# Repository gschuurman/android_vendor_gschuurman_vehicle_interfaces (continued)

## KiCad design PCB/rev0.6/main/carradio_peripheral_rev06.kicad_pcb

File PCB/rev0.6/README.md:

# PCB rev 0.6: main board with a K-line module socket

Rev 0.6 is rev 0.5 (`../rev0.5/`, kept as the reference) plus a socket for a stackable K-line module. The GNSS and
audio modules are the rev 0.4 boards (`../rev0.4/gnss|audio`); the USB module is `usb/` (rev 0.4 with the fix below). Everything in
`../rev0.5/README.md` (USB_UP pair, TPS560430 layout, expansion pins) and `../rev0.4/README.md` still applies except
J10 and the VIM3 power key, described here.

Everything to order and hand-assemble the four boards is in `order/` (see `order/ORDER_INSTRUCTIONS.md`); `fab/` holds
the same Gerbers plus JLC assembly BOM/CPL files in case of a PCBA order.

## USB module rev 0.6

`usb/carradio_usb_rev06.*` is the rev 0.4 USB module with solid zone connections on the GND pads of the 5 V / 3 A buck
U15 (LMR33630, pin 1 and the PowerPAD), the port switch U16 (TPS2561, pin 1 and the exposed pad) and C69. KiCad 10 had
flagged them as starved thermals. DRC: 0 unconnected, no errors.

## Impedance-controlled pairs (JLCPCB calculator)

JLCPCB's impedance calculator for JLC04161H-7628 (L1 over L2) gives 0.334 / 0.300 mm for 90 Ω and 0.2187 / 0.20 mm
for 100 Ω edge-coupled pairs. Rev 0.6 uses them:

- **USB_UP** (VIM3 to hub 1): re-routed at **0.32 mm / 0.30 mm gap** (rev 0.5: 0.30 / 0.15; the tight gap put it
  below 90 Ω). 0.32 instead of 0.334 so the pair fits the gap between U13's pins and the J23 socket; that is about 1 Ω
  higher. DP 51.3 mm, DM 53.2 mm. The In1 keep-out under it is 0.5 mm each side, opened at U13's pin escapes and for
  two vias beside the pair (`pairkeep.py` BUF / EXCLUDE_FP / EXCLUDE_XY).
- **HDMI** D0, D1, D2, CLK (J13 to J14): rebuilt by `hdmipairs.py` as coupled **0.2187 mm / 0.20 mm** pairs. Before
  they were 0.20 mm traces 0.80 mm apart (about 140 Ω, each trace closer to the neighbouring pair than to its partner).
  Each pair now runs centred over its GND pin with a short 45° jog at both connectors; P/N lengths match within 0.69 mm
  (about 5 ps).
- Net classes in the project: USB 0.32 / 0.30, HDMI 0.2187 / 0.20.

## J10: K-line module socket

In rev 0.5, J10 was a 1x8 male header under the USB module with no battery voltage. Now it is a **2x4 female socket,
8.5 mm tall** (same family as J23/J25/J27) at (82, 29) mm, in the free strip between the HDMI pairs and the USB module.
A K-line module stacks on it like the other modules: male header on its underside, about 11 mm above the main board,
held by one **M2 standoff at H8 (69.6, 18.5)**.

| Pin | Net | Pin | Net |
|---|---|---|---|
| 1 | +3V3_MCU | 2 | GND |
| 3 | EXP_GP32: RP2350B UART TX (to the transceiver TXD) | 4 | EXP_GP33: UART RX (from RXD) |
| 5 | EXP_GP28: enable / sleep, or an L-line driver | 6 | GND |
| 7 | VBAT_KLINE: protected battery voltage through F6 | 8 | +5V_AON (if the transceiver wants 5 V) |

- **F6** (BHFUSE BSMD1206-020-30V, LCSC C883118, 200 mA hold / 460 mA trip) feeds pin 7 from VBAT_P (after the
  reverse-polarity diode and load-dump TVS). A fault on the module trips F6, not F1, so the always-on 5 V supply and
  the MCU keep running.
- **Module outline:** up to about 25 x 17 mm, over x 67-91, y 15-32 mm on the main board. That clears the HDMI
  connector J13 (top), the screen FPC J14 and its latch (right edge) and the USB module (below y 32.5). The parts under
  it are low SMD parts and the HDMI pairs, which the module only flies over. Socket pin 1 is at (78.19, 27.63).
- **Car side:** the module brings the K-line in through its own connector, e.g. a JST to the OBD-II socket
  (pin 7 K-line, pins 4/5 GND). Pin 16 is not needed because VBAT comes from J10 pin 7.
- **Transceiver:** a K-line part such as ST L9637D or a LIN transceiver such as TJA1021 (LIN is electrically close and
  often used for K-line at 10.4 kbaud). Check that TXD accepts 3.3 V logic and RXD is open-drain or 3.3 V compatible;
  pull RXD up to J10 pin 1.
- **Firmware:** UART on GPIO32/33 at 10.4 kbaud; for the ISO 9141 / KWP2000 slow init, switch GPIO32 to SIO and
  bit-bang the 5-baud address byte. GPIO28 drives enable/sleep.

The socket and standoff stay outside the HDMI corridor (In1 "HDMI reference" keep-out), so the HDMI ground reference
is untouched. J21 (SPI1 + I2C under the USB module) is unchanged from rev 0.5.

## VIM3 power key: PhotoMOS U22

The VIM3 POWER key is pressed by a PhotoMOS that shorts the key's own two pins, isolated, as in the earlier hand-wired
setup. Up to rev 0.5, Q1 (AO3400A) pulled J5 pin 1 to the board's GND.

- **U22**: Panasonic **AQY210S** (SOP-4, 350 V / 120 mA, 25 Ω max on), on the **bottom side** right next to J5 at
  (19.2, 15.0). Pins 3/4 (the switch) go to J5 pins 1/2 over a few mm of bottom copper; pin 2 (LED cathode) to GND.
- **R12**: 390 Ω from GPIO15 (`MCU_PWR_KEY`) to the LED anode, about 5 mA from 3.3 V. The AQY210S needs 3 mA at most
  to switch on. The GPIO's default 4 mA drive is fine; the 8 mA setting gives more margin. Firmware is unchanged:
  GPIO15 high = key pressed.
- **R19** (the MOSFET's gate pull-down) is gone: an undriven LED is off.
- **J5** (JST-PH 2P): pins 1 and 2 go to the two pads of the VIM3 POWER key. Either way round works, J5 no longer
  carries GND.
- Scripts: `layout/schematic/pwrkey_sch.py` (schematic) and `layout/main/pwrkeypcb.py` (place U22, rip the old
  copper), then `bridge.py` routed `/VIM3_PWR_KEY_A`, `/VIM3_PWR_KEY_B` and `/PWR_KEY_LED`. DRC: 0 unconnected, no
  errors; schematic parity unchanged (field mismatches only).

## Status

- Main board: DRC 0 unconnected, no errors (warnings: silkscreen, unused fan-out stubs); schematic parity same as rev 0.5.
- USB module rev 0.6: DRC 0 unconnected, no errors. GNSS module: clean. Audio module: one starved-thermal warning on
  the through-hole header J24 pin 3 (fine for hand soldering).

## Bring-up wizards

Step-by-step bench wizards (multimeter first, then first power): `main/WIZARD.html`, `usb/WIZARD.html`,
`../rev0.4/gnss/WIZARD.html` and `../rev0.4/audio/WIZARD.html`. See `../wizard/README.md`.

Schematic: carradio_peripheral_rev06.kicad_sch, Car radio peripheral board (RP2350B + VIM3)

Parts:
C1, C49, C50: 10uF 50V; C_1206_3216Metric; MPN 1206 10uF 50V X5R (Murata GRM31CR61H106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; LCSC C77092
C2, C3, C5, C6, C7, C8, C9, C10, C11, C42, C43, C44, C45, C47, C51, C52, C63, C85, C86, C87, C88, C89, C90, C91, C92, C93, C94, C95, C96, C97, C98, C101, C102, C103: 100nF; C_0603_1608Metric; MPN 0603 100nF 50V X7R; LCSC C14663
C4, C56, C57, C58, C59: 22uF; C_0805_2012Metric; MPN 0805 22uF 25V X5R; LCSC C45783
C12, C13, C61, C80: 1uF; C_0603_1608Metric; MPN 0603 1uF 50V X5R (Murata GRM188R61H105K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; LCSC C77386
C46, C62, C81: 10uF; C_0805_2012Metric; MPN 0805 10uF 25V X5R; LCSC C15850
C48: 100uF 50V; CP_Elec_8x10; MPN Panasonic EEEFK1H101P 100uF 50V 8x10.2; LCSC C178548
C53, C82, C83, C84: 4.7uF; C_0603_1608Metric; MPN 0603 4.7uF 16V X5R; LCSC C19666
C54: 4.7nF; C_0603_1608Metric; MPN 0603 4.7nF 50V X7R; LCSC C53987
C55: 22pF; C_0603_1608Metric; MPN 0603 22pF 50V C0G; LCSC C1653
C60: 220uF 10V polymer; CP_Elec_6.3x7.7; MPN Lelon OVZ221M1CTR-0608 polymer 220uF 16V; LCSC C881921
C99, C100: 15pF; C_0603_1608Metric; MPN Samsung CL10C150JB8NNNC 15pF C0G; LCSC C1644
C104: 1nF; C_0603_1608Metric; MPN Samsung CL10B102KB8NNNC 0603 1nF 50V X7R; LCSC C1588
D1, D4, D9: SS34; D_SMA; MPN SS34 40V 3A Schottky; LCSC C8678
D2, D5, D13: SMBJ22A; D_SMB; MPN SMBJ22A (BORN); alt DOWO C284010; LCSC C151920
D6, D7, D11, D12: 1N4148W; D_SOD-123; MPN 1N4148W; LCSC C81598
D8, D15: BZT52C12; D_SOD-123; MPN BZT52C12-7-F 12V zener; LCSC C124196
D10, D16: LED green; LED_0805_2012Metric; MPN KT-0805G green LED; LCSC C2297
D14: Load-dump TVS; D_SMC; MPN Liown 5.0SMDJ22A, 5 kW SMC; LCSC C2990362
F1, F3: PTC 0.5A hold 30V; Fuse_1206_3216Metric; MPN BHFUSE BSMD1206-050-30V; LCSC C883126
F2: PTC 0.75A hold 30V; Fuse_1812_4532Metric; MPN Littelfuse 1812L075/33DR; LCSC C151170
F4: 7.5A fuse; Littelfuse_01530008Z; MPN Littelfuse 01530008Z mini blade holder 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; LCSC C206907
F6: PTC 0.2A hold 30V; Fuse_1206_3216Metric; MPN BHFUSE BSMD1206-020-30V; LCSC C883118
J1: ISO 10487 A (via pigtail); Molex_Micro-Fit_3.0_43045-0812_2x04_P3.00mm_Vertical; MPN Molex 43045-0812; LCSC C277661
J2: VIM3 40-pin via 2x20 IDC ribbon; IDC-Header_2x20_P2.54mm_Vertical; MPN BOOMELE 2.54-2*20P box header (check it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; LCSC C9138
J5: VIM3 POWER key lead; JST_PH_B2B-PH-K_1x02_P2.00mm_Vertical; MPN JST B2B-PH-K-S; LCSC C131337
J7: BH1750 light sensor; JST_PH_B4B-PH-K_1x04_P2.00mm_Vertical; MPN JST B4B-PH-K-S; LCSC C131334
J8: ISO 10487 C1 (via pigtail); Molex_Micro-Fit_3.0_43045-0612_2x03_P3.00mm_Vertical; MPN Molex 43045-0612; LCSC C234188
J10: K-line module socket; PinSocket_2x04_P2.54mm_Vertical; MPN 2x4 2.54mm female socket, 8.5mm body (s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
J12: Display buttons; JST_PH_B5B-PH-K_1x05_P2.00mm_Vertical; MPN JST B5B-PH-K-S; LCSC C157993
J13: HDMI in (from VIM3); HDMI_A_Amphenol_10029449-x01xLF_Horizontal; MPN Amphenol 10029449-111RLF (plating varia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; LCSC C427307
J14: Display FPC 40P 0.5mm; XUNPU_FPC-05FB-40PH20; MPN XUNPU FPC-05FB-40PH20, 40P 0.5mm dual-c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; LCSC C2856837
J18: VIM3 VIN (JST-XH 2P); JST_XH_B2B-XH-A_1x02_P2.50mm_Vertical; MPN JST B2B-XH-A; LCSC C158012
J21: Expansion 2; PinHeader_1x10_P2.54mm_Vertical; MPN BOOMELE 1x10 male header 2.54mm; LCSC C57369
J22: SWD; PinHeader_1x04_P2.54mm_Vertical; MPN 1x4 male header 2.54mm; LCSC C124378
J23: Audio module socket; PinSocket_2x10_P2.54mm_Vertical; MPN BOOMELE 2.54-2*10P female 8.5mm (LCSC o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; LCSC C30867
J25: USB module socket; PinSocket_2x10_P2.54mm_Vertical; MPN BOOMELE 2.54-2*10P female 8.5mm (LCSC o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; LCSC C30867
J27: GNSS module socket; PinSocket_2x08_P2.54mm_Vertical; MPN 2x8 2.54mm female socket, 8.5mm body (s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
JP1: SERVICE jumper; PinHeader_1x02_P2.54mm_Vertical; MPN 1x2 male header 2.54mm + jumper cap C53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; LCSC C124375
JP2: GNSS RX source; SolderJumper-3_P1.3mm_Bridged12_RoundedPad1.0x1.5mm; MPN 3-pad solder jumper (PCB copper, no par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
L1: 18uH; L_Sunlord_SWPA4030S; MPN SWPA4030S180MT 18uH; LCSC C96895
L3: 4.7uH 12A+; L_Bourns_SRP1245A; MPN Bourns SRP1265A-4R7M 4.7uH Isat 28A 8.4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; LCSC C780205
L5: 3.3uH; L_Murata_DFE201610P; MPN Abracon AOTA-B201610S3R3-101-T 3.3uH (R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; LCSC C42411119
NT1, NT2, NT3: NetTie; NetTie-2_SMD_Pad0.5mm; MPN net tie (copper only, not a part)
Q2: P-MOSFET -60V; SOT-23; MPN onsemi FDN5618P -60V P-MOSFET (check 1=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; LCSC C400792
Q3: 2N7002; SOT-23; MPN JSCJ 2N7002; LCSC C8545
Q10: P-MOSFET -40V; TO-252-2; MPN NCE40P70K -40V 10 mOhm P-MOSFET TO-252 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; LCSC C130101
Q11, Q12: CSD18543Q3A; VSON-8_3.3x3.3mm_P0.65mm_NexFET; MPN TI CSD18543Q3A 60V 8.5mOhm N-MOSFET; LCSC C840100
R1, R15, R35, R70, R72, R96: 100k; R_0603_1608Metric; MPN 0603 100k 1%; LCSC C25803
R2: 24k; R_0603_1608Metric; MPN 0603 24k 1%; LCSC C23352
R3, R5, R29, R31: 4.7kΩ 0805; R_0805_2012Metric; MPN 0805 4.7k 1%; LCSC C17673
R4, R6, R8, R9, R18, R30, R32, R33, R34, R94, R95: 4.7k; R_0603_1608Metric; MPN 0603 4.7k 1%; LCSC C23162
R7, R37, R38, R39, R40, R46, R59, R61, R63, R65, R73, R79, R81, R82, R86, R90, R100, R101: 1k; R_0603_1608Metric; MPN 0603 1k 1%; LCSC C21190
R10: 1M; R_0603_1608Metric; MPN 0603 1M 1%; LCSC C22935
R11: 220k; R_0603_1608Metric; MPN 0603 220k 1%; LCSC C22961
R12: 390Ω; R_0603_1608Metric; MPN UNI-ROYAL 0603WAF3900T5E 390 1%; LCSC C23151
R13, R14, R47, R58, R60, R62, R64, R66, R85, R87, R88, R89, R91, R92, R93, R104: 10k; R_0603_1608Metric; MPN 0603 10k 1%; LCSC C25804
R16, R23, R24: 100Ω; R_0603_1608Metric; MPN 0603 100 1%; LCSC C22775
R42, R43, R44, R45, R80: 33Ω; R_0603_1608Metric; MPN 0603 33 1%; LCSC C23140
R56, R67: 0Ω; R_0603_1608Metric; MPN 0603 0 1%; LCSC C21189
R57: 0Ω; R_0603_1608Metric; MPN 0603 0 1%; LCSC C21189; not fitted
R68: 47k; R_0603_1608Metric; MPN 0603 47k 1% (YAGEO RC0603FR-0747KL); LCSC C105579
R69: 30k; R_0603_1608Metric; MPN UNI-ROYAL 0603WAF3002T5E; LCSC C22984
R71: 8.2k; R_0603_1608Metric; MPN 0603 8.2k 1%; LCSC C25981
R74: 10mΩ 2512; R_2512_6332Metric; MPN Yageo PA2512FKE7T0R01E 10 mOhm 1% 3W; LCSC C375691
R83, R84: 27Ω; R_0603_1608Metric; MPN FOJAN FRC0603F27R0TS 27R 1%; LCSC C2907021
R97, R98: 0Ω; R_0402_1005Metric; MPN UNI-ROYAL 0402WGF0000TCE 0402 0R; LCSC C17168
R99: 2.2Ω 0805; R_0805_2012Metric; MPN UNI-ROYAL 0805W8F220KT5E 0805 2.2R 125mW; LCSC C17521
SW1: BOOTSEL; SW_SPST_TL3342; MPN E-Switch TL3342F160QG; LCSC C2886898
SW2: RESET; SW_SPST_TL3342; MPN E-Switch TL3342F160QG; LCSC C2886898
TH1: NTC 10k B3950; R_0603_1608Metric; MPN Murata NCP18XH103F03RB 10k B3380 0603; LCSC C13564
U1: TPS560430XDBVR; SOT-23-6; MPN TPS560430XDBVR 36V 600mA buck, 1.1MHz; LCSC C524782
U2, U3, U4, U5: EL817S1(C); SMDIP-4_W7.62mm; MPN EL817S1(C)(TU)-F (EL817S1(C)(TU)-FV); LCSC C470884
U6: LP5907MFX-3.3; SOT-23-5; MPN TI LP5907MFX-3.3/NOPB 250mA LDO (TECH P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; LCSC C5370990
U12: TPS55288RPMR; TPS55288RPMR_VQFN-HR-26; MPN TI TPS55288RPMR; LCSC C2864583
U13: CH334R; QSOP-16_3.9x4.9mm_P0.635mm; MPN WCH CH334R 4-port USB 2.0 hub, QSOP-16; LCSC C4154405
U19: AP2112K-3.3; SOT-23-5; MPN Diodes AP2112K-3.3TRG1; LCSC C51118
U20: RP2350B; QFN-80-1EP_10x10mm_P0.4mm_EP3.4x3.4mm; MPN Raspberry Pi RP2350B QFN-80 (LCSC stock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; LCSC C42415655
U21: W25Q128JVS; SOIC-8_5.3x5.3mm_P1.27mm; MPN Winbond W25Q128JVSIQ; LCSC C97521
U22: AQY210S; SO-4_4.4x4.3mm_P2.54mm; MPN Panasonic AQY210S PhotoMOS 350V 120mA 1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
Y1: 12MHz; Crystal_SMD_3225-4Pin_3.2x2.5mm; MPN YXC X322512MSB4SI 12MHz; LCSC C9002
Y3: 12MHz; Crystal_SMD_3225-4Pin_3.2x2.5mm; MPN Abracon ABM8-272-T3 12MHz (Raspberry Pi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; LCSC C20625731

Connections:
/+1V1_MCU: C83.1, C93.1, C94.1, C95.1, L5.2, U20.10 (DVDD), U20.32 (DVDD), U20.51 (DVDD), U20.65 (VREG_FB)
/+3V3_GNSS: C13.1, J27.1, J27.2, U6.5 (OUT)
/+3V3_MCU: C8.1, C81.1, C82.1, C85.1, C86.1, C87.1, C88.1, C89.1, C90.1, C91.1, C92.1, C96.1, C97.1, C98.1, J7.1, J10.1, J21.1, J27.4, JP1.1, R33.1, R34.1, R58.1, R60.1, R62.1, R64.1, R80.1, R85.1, R87.1, R88.1, R89.1, R93.1, U2.4, U3.4, U4.4, U5.4, U19.5 (VOUT), U20.5 (IOVDD), U20.15 (IOVDD), U20.24 (IOVDD), U20.29 (IOVDD), U20.41 (IOVDD), U20.50 (IOVDD), U20.59 (ADC_AVDD), U20.60 (IOVDD), U20.64 (VREG_VIN), U20.68 (USB_OTP_VDD), U20.69 (QSPI_IOVDD), U20.76 (IOVDD), U21.8 (VCC)
/+5V_AON: C4.1, C12.1, C61.1, C80.1, J10.8, L1.2, R1.1, U6.1 (IN), U13.12 (V5), U19.1 (VIN), U19.3 (EN)
/+5V_SYS: C46.1, C47.1, J14.4, J14.5, J14.6, J18.1, J25.5, J25.6, NT2.2, R74.2, R91.1
/ACC_F: D4.2 (A), F2.2
/ACC_LED: D6.1 (K), R3.2, U2.1
/ACC_P: C5.1, D4.1 (K), D5.1 (K), D8.1 (K), Q2.2 (S), R3.1, R13.1, R31.1
/ACC_RAW: F2.1, J1.7
/AMP_CTRL: Q3.1 (G), R15.1, R16.2
/AMP_G: D8.2 (A), Q2.1 (G), R13.2, R14.1
/AMP_LED: D10.2 (A), R18.2
/AMP_PULL: Q3.3 (D), R14.2
/AMP_REM: D9.1 (K), D13.1 (K), F3.2, J1.3, J8.6, R18.1, R57.1
/AMP_SW: F3.1, Q2.3 (D)
/BATT_F: D1.2 (A), F1.2
/BATT_F2: F4.2, Q10.2 (D)
/BATT_RAW: F1.1, F4.1, J1.4
/BB_AGND: C54.2, C55.2, NT3.1, R67.2, R68.2, R69.2, R70.2, U12.7 (DITH/SYNC), U12.10 (AGND)
/BB_BOOT1: C51.1, U12.22 (BOOT1)
/BB_BOOT2: C52.1, U12.20 (BOOT2)
/BB_CDC: R70.1, U12.16 (CDC)
/BB_COMP: C55.1, R71.1, U12.18 (COMP)
/BB_COMP_RC: C54.1, R71.2
/BB_DR1H: R97.1, U12.2 (DR1H)
/BB_DR1H_G: Q11.4 (G), R97.2
/BB_DR1L: R98.1, U12.1 (DR1L)
/BB_DR1L_G: Q12.4 (G), R98.2
/BB_FSW: R68.1, U12.8 (FSW)
/BB_ILIM: R69.1, U12.17 (ILIM)
/BB_ISN: NT2.1, U12.13 (ISN)
/BB_ISP: NT1.1, U12.12 (ISP)
/BB_MODE: R67.1, U12.15 (MODE)
/BB_SNUB: C104.2, R99.1
/BB_SW1: C51.2, C104.1, L3.1, Q11.1 (S), Q11.2 (S), Q11.3 (S), Q12.5 (D), U12.23 (SW1)
/BB_SW2: C52.2, L3.2, U12.21 (SW2), U12.25 (SW2)
/BB_VCC: C53.1, U12.19 (VCC)
/BB_VOUT: C56.1, C57.1, C58.1, C59.1, C60.1, NT1.2, R74.1, U12.11 (VOUT), U12.26 (VOUT)
/BL_EN: J14.37, R23.2
/BL_PWM: J14.36, R24.2
/BOOTSEL_SW: R81.2, SW1.1
/BTN_MUTE: J12.4, R65.1
/BTN_SCREEN: J12.1, R59.1
/BTN_VOLDN: J12.3, R63.1
/BTN_VOLUP: J12.2, R61.1
/BUCK_CB: C3.1, U1.1 (CB)
/BUCK_FB: R1.2, R2.1, U1.3 (FB)
/BUCK_SW: C3.2, L1.1, U1.6 (SW)
/DAC_XSMT: J23.12, R46.2, R47.1
/EXP_GP24: J21.9, U20.25 (GPIO24)
/EXP_GP25: J21.8, U20.26 (GPIO25)
/EXP_GP26: J21.7, U20.27 (GPIO26)
/EXP_GP27: J21.6, U20.28 (GPIO27)
/EXP_GP28: J10.5, U20.36 (GPIO28)
/EXP_GP32: J10.3, U20.40 (GPIO32)
/EXP_GP33: J10.4, U20.42 (GPIO33)
/GNSS_PPS: J27.14, R40.1
/GNSS_RST: J27.13, R39.2
/GNSS_RXD: J27.10, JP2.2 (C)
/GNSS_RXD_MCU: JP2.3 (B), R37.2
/GNSS_RXD_VIM: JP2.1 (A), R101.2
/GNSS_SAFEBOOT: J27.15, R79.2
/GNSS_TXD: J27.8, R38.1, R100.1
/GNSS_USB_DM: J27.9, U13.3 (DM3-)
/GNSS_USB_DP: J27.7, U13.4 (DP3+)
/HDMI_5V: J13.18 (+5V), J14.27
/HDMI_CEC: J13.13 (CEC), J14.23
/HDMI_CLKN: J13.12 (CK-), J14.22
/HDMI_CLKP: J13.10 (CK+), J14.20
/HDMI_D0N: J13.9 (D0-), J14.19
/HDMI_D0P: J13.7 (D0+), J14.17
/HDMI_D1N: J13.6 (D1-), J14.16
/HDMI_D1P: J13.4 (D1+), J14.14
/HDMI_D2N: J13.3 (D2-), J14.13
/HDMI_D2P: J13.1 (D2+), J14.11
/HDMI_HPD: J13.19 (HPD), J14.28
/HDMI_SCL: J13.15 (SCL), J14.24
/HDMI_SDA: J13.16 (SDA), J14.25
/HUB1_RST: R90.2, R104.2, U13.9 (~RESET/CDP)
/HUB2_UP_DM: J25.12, U13.1 (DM4-)
/HUB2_UP_DP: J25.10, U13.2 (DP4+)
/HUB_3V3: C62.1, C63.1, R104.1, U13.13 (VDD33)
/HUB_XI: U13.16 (XI), Y1.1
/HUB_XO: U13.15 (XO), Y1.3
/I2S_BCLK: J23.5, R42.2
/I2S_DOUT0: J23.9, R44.2
/I2S_DOUT1: J23.10, R45.2
/I2S_LRCK: J23.7, R43.2
/ILLUM_LED: D7.1 (K), R5.2, U3.1
/ILLUM_RAW: J1.6, R5.1
/ISO_A5: J1.5, R57.2
/LINE_FL: J8.3, J23.17
/LINE_FR: J8.4, J23.18
/LINE_GND: J8.5, R56.1
/LINE_RL: J8.1, J23.19
/LINE_RR: J8.2, J23.20
/LUX_SCL: J7.3, J21.3, J23.13, R33.2, U12.5 (SCL), U20.39 (GPIO31)
/LUX_SDA: J7.4, J21.2, J23.14, R34.2, U12.6 (SDA), U20.38 (GPIO30)
/MCU_5VSYS_ADC: C102.1, R91.2, R92.1, U20.52 (GPIO41/ADC1)
/MCU_ACC_IN: C6.1, R4.1, U2.3, U20.54 (GPIO43/ADC3)
/MCU_AMP_EN: R16.1, U20.20 (GPIO20)
/MCU_BL_EN: R23.1, R96.1, U20.77 (GPIO0)
/MCU_BL_PWM: R24.1, U20.78 (GPIO1)
/MCU_BTN_MUTE: C45.1, R64.2, R65.2, U20.16 (GPIO16)
/MCU_BTN_SCREEN: C42.1, R58.2, R59.2, U20.18 (GPIO18)
/MCU_BTN_VOLDN: C44.1, R62.2, R63.2, U20.22 (GPIO22)
/MCU_BTN_VOLUP: C43.1, R60.2, R61.2, U20.17 (GPIO17)
/MCU_DAC_MUTE: R46.1, U20.8 (GPIO10)
/MCU_GNSS_EN: R35.1, U6.3 (EN), U20.7 (GPIO9)
/MCU_GNSS_PPS: R40.2, R94.1, U20.80 (GPIO3)
/MCU_GNSS_RST: R39.1, U20.4 (GPIO7)
/MCU_GNSS_RX: R38.2, R95.1, U20.2 (GPIO5)
/MCU_GNSS_SAFEBOOT: R79.1, U20.6 (GPIO8)
/MCU_GNSS_TX: R37.1, U20.1 (GPIO4)
/MCU_HUB_RST: R90.1, U20.79 (GPIO2)
/MCU_ILLUM_IN: C7.1, R6.1, U3.3, U20.46 (GPIO37)
/MCU_LED: R86.1, U20.21 (GPIO21)
/MCU_LED_K: D16.2 (A), R86.2
/MCU_PARK_IN: C11.1, R32.1, U5.3, U20.13 (GPIO14)
/MCU_PWR_KEY: R12.1, U20.14 (GPIO15)
/MCU_REV_IN: C10.1, R30.1, U4.3, U20.44 (GPIO35)
/MCU_RUN: C101.1, J22.4, R85.2, SW2.1, U20.35 (RUN)
/MCU_SBC_SENSE: R7.2, R8.1, U20.3 (GPIO6)
/MCU_SERVICE: JP1.2, R9.1, U20.19 (GPIO19)
/MCU_SWCLK: J22.1, U20.33 (SWCLK)
/MCU_SWDIO: J22.3, U20.34 (SWDIO)
/MCU_TEMP_ADC: C103.1, R93.2, TH1.1, U20.53 (GPIO42/ADC2)
/MCU_USBP_FAULT1: J25.18, R87.2, U20.48 (GPIO39)
/MCU_USBP_FAULT2: J25.17, R88.2, U20.47 (GPIO38)
/MCU_USBP_PG: J25.15, R89.2, U20.45 (GPIO36)
/MCU_USB_DM: R83.2, U13.7 (DM1-)
/MCU_USB_DM_R: R83.1, U20.66 (USB_DM)
/MCU_USB_DP: R84.2, U13.8 (DP1+)
/MCU_USB_DP_R: R84.1, U20.67 (USB_DP)
/MCU_VBAT_ADC: C9.1, R10.2, R11.1, U20.49 (GPIO40/ADC0)
/MCU_VIM3_PWR_EN: R73.1, U20.23 (GPIO23)
/MCU_VREG_AVDD: C84.1, R80.2, U20.61 (VREG_AVDD)
/MCU_VREG_LX: L5.1, U20.63 (VREG_LX)
/MCU_XIN: C99.1, U20.30 (XIN), Y3.1
/MCU_XOUT: R82.1, U20.31 (XOUT)
/MCU_XTAL_R: C100.1, R82.2, Y3.3
/PARK_K: D12.2 (A), U5.2
/PARK_LED: R31.2, U5.1
/PARK_RAW: D12.1 (K), J1.2
/PWR_KEY_LED: R12.2, U22.1
/QSPI_SCLK: U20.71 (QSPI_SCLK), U21.6 (CLK)
/QSPI_SD0: U20.72 (QSPI_SD0), U21.5 (DI(IO0))
/QSPI_SD1: U20.74 (QSPI_SD1), U21.2 (DO(IO1))
/QSPI_SD2: U20.73 (QSPI_SD2), U21.3 (IO2)
/QSPI_SD3: U20.70 (QSPI_SD3), U21.7 (IO3)
/QSPI_SS: R81.1, U20.75 (~QSPI_SS), U21.1 (~CS)
/REV_LED: D11.1 (K), R29.2, U4.1
/REV_RAW: J1.1, R29.1
/RPP_G: D15.2 (A), Q10.1 (G), R66.1
/TOUCH_DN: J14.34, U13.5 (DM2-)
/TOUCH_DP: J14.33, U13.6 (DP2+)
/USB_UP_DM: J2.5 (V3:USB_DM), U13.10 (DMU-)
/USB_UP_DP: J2.7 (V4:USB_DP), U13.11 (DPU+)
/VBAT_KLINE: F6.2, J10.7
/VBAT_P: C1.1, C2.1, D1.1 (K), D2.1 (K), F6.1, R10.1, U1.4 (EN), U1.5 (VIN)
/VIM3_3V3: J2.14 (V27:3V3), J2.39 (V20:3V3), R7.1
/VIM3_5V: J2.1 (V1:5V), J2.3 (V2:5V), J23.1, J23.2
/VIM3_I2S_BCLK: J2.18 (V29:TDMB_SCLK), R42.1
/VIM3_I2S_DOUT0: J2.22 (V31:TDMB_DOUT0), R44.1
/VIM3_I2S_DOUT1: J2.26 (V33:TDMB_DOUT1), R45.1
/VIM3_I2S_DOUT2: J2.30 (V35:TDMB_DOUT3), J23.11
/VIM3_I2S_LRCK: J2.24 (V32:TDMB_FS), R43.1
/VIM3_I2S_MCLK: J2.20 (V30:TDMB_MCLK), J23.8
/VIM3_PWR_EN: J25.16, R72.1, R73.2, U12.4 (EN/UVLO)
/VIM3_PWR_KEY_A: J5.1, U22.3
/VIM3_PWR_KEY_B: J5.2, U22.4
/VIM3_UARTC_RX: J2.29 (V15:UARTC_RX), R100.2
/VIM3_UARTC_TX: J2.31 (V16:UARTC_TX), R101.1
/VSYS_IN: C48.1, C49.1, C50.1, D14.1 (K), D15.1 (K), J25.1, J25.2, Q10.3 (S), Q11.5 (D), U12.3 (VIN)
GND: C1.2, C2.2, C4.2, C5.2, C6.2, C7.2, C8.2, C9.2, C10.2, C11.2, C12.2, C13.2, C42.2, C43.2, C44.2, C45.2, C46.2, C47.2, C48.2, C49.2, C50.2, C53.2, C56.2, C57.2, C58.2, C59.2, C60.2, C61.2, C62.2, C63.2, C80.2, C81.2, C82.2, C83.2, C84.2, C85.2, C86.2, C87.2, C88.2, C89.2, C90.2, C91.2, C92.2, C93.2, C94.2, C95.2, C96.2, C97.2, C98.2, C99.2, C100.2, C101.2, C102.2, C103.2, D2.2 (A), D5.2 (A), D6.2 (A), D7.2 (A), D9.2 (A), D10.1 (K), D11.2 (A), D13.2 (A), D14.2 (A), D16.1 (K), J1.8, J2.2 (V21:GND), J2.8 (V24:GND), J2.9 (V5:GND), J2.16 (V28:GND), J2.17 (V9:GND), J2.27 (V14:GND), J2.28 (V34:GND), J2.33 (V17:GND), J2.40 (V40:GND), J7.2, J10.2, J10.6, J12.5, J13.2 (D2S), J13.5 (D1S), J13.8 (D0S), J13.11 (CKS), J13.17 (GND), J13.SH, J14.8, J14.9, J14.10, J14.12, J14.15, J14.18, J14.21, J14.26, J14.35, J14.MP (MountPin), J18.2, J21.10, J22.2, J23.3, J23.4, J23.6, J23.15, J23.16, J25.3, J25.4, J25.7, J25.8, J25.13, J25.14, J25.20, J27.3, J27.6, J27.11, J27.12, J27.16, NT3.2, Q3.2 (S), Q12.1 (S), Q12.2 (S), Q12.3 (S), R2.2, R4.2, R6.2, R8.2, R9.2, R11.2, R15.2, R30.2, R32.2, R35.2, R47.2, R56.2, R66.2, R72.2, R92.2, R94.2, R95.2, R96.2, R99.2, SW1.2, SW2.2, TH1.2, U1.2 (GND), U2.2, U3.2, U4.2, U6.2 (GND), U12.9 (PGND), U12.24 (PGND), U13.14 (GND), U19.2 (GND)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; also elsewhere on the board

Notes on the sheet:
1. ISO 10487 CONNECTOR A (power) + ALWAYS-ON 5V FOR PICO AND GNSS
J1 pad n = ISO A pin n. A1 REVERSE A2 HANDBRAKE A3 AMP REMOTE A4 BATT+ A5 remote (R57) A6 ILLUM A7 ACC A8 GND
Always-on 5.2V: MCU VSYS + GNSS LDO. TPS560430X runs PFM at light load (~55uA Iq).
2. VEHICLE INPUTS (opto-isolated). ACC, ILLUM, REVERSE: +12V = on. PARK: switch to ground = on.
ACC (ISO A7)
ILLUM (ISO A6)
REVERSE lamp (ISO A1)
PARK (ISO A2, handbrake switch; may stay unwired)
LED ~2.7mA at 14.4V; EL817 C-grade CTR >= 200%. 4.7k pull-downs satisfy RP2350-E9.
3. AMPLIFIER REMOTE (+12V from ACC, MCU GP20)
Goes to ISO A3 and C1-6 (A5 via R57). ~1A capable; remote inputs draw <100mA.
Only works while ACC is on, even if the MCU hangs.
4. MCU HELPERS (MCU core is section 13)
GPIO map: see section 13 and DESIGN_rev03.md.
5. GNSS MODULE: u-blox NEO-M9N, active antenna on U.FL (pigtail to SMA), UART + USB to the main board. Switched 3.3V supply stays on the main board.
6. VIM3 POWER KEY, BACKLIGHT, LIGHT SENSOR (all from the MCU)
Backlight and reverse moved off the VIM3 header; the VHAL now sets/reads them through the MCU.
Display buttons (to GND): GP18 screen, GP17 vol+, GP22 vol-, GP16 mute. J12.
I2S series resistors at the ribbon entry.
8. VIM3 40-PIN HEADER + ISO 10487 C1 (line out)
VIM3 pin v -> IDC pad 2v-1 (v<=20) or 2(v-20) (v>20). Pin 1 sits opposite pin 21 (confirmed by Glenn).
Pins 30 (TDM-B MCLK) and 35 (TDM-B lane 3) go straight to the audio module socket J23 as spares.
J8 pad n = ISO C1 pin n: 1 RL, 2 RR, 3 FL, 4 FR, 5 line GND, 6 remote +12V.
9. DISPLAY: Waveshare 7in 70H-1024600 adapter built in (HDMI in from VIM3 -> 40-pin FPC to the panel)
Panel 5V (~0.45A) comes from the board's switched 5V rail (+5V_SYS, section 10), not from VIM3 USB. Touch USB goes to the on-board hub (section 11).
Backlight EN/PWM now go straight to the panel: 0V = brightest, 3.3V = darkest (invert PWM in firmware). J6 removed.
FPC orientation as on the Waveshare adapter: seen from the top, ribbon leaving the board edge, pin 1 is on the RIGHT, pin 40 on the left.
10. 5V/5A SYSTEM SUPPLY FOR VIM3 + SCREEN + HUB (TPS55288 buck-boost, rides through cranking and overvoltage)
Input 3V-36V (runs through cranking); output 5.0V up to 5A. MCU GP23 = EN, MCU I2C1 sets OE/voltage/current limit.
VIN is permanent +12V so the VIM3 can finish its Android shutdown after ACC drops.
11. USB HUB: VIM3 header USB (pins 3/4) -> MCU, screen touch, spare port
Hub 1 runs from the always-on +5V_AON so a blank MCU enumerates (first flash over USB). One link to the VIM3: no USB cables. Port 1 MCU, 2 touch, 3 GNSS module USB, 4 second hub (external ports + RTL-SDR). Route D+/D- as 90 ohm pairs.
VIM3 header pins 3/4 are a working USB host port (confirmed by Glenn, 2026-09-29).
13. MCU: RP2350B (QFN-80) + 16MB QSPI flash + 12MHz crystal + 3.3V LDO, per the Raspberry Pi Pico 2 reference design
rev 0.4: GPIO map re-assigned for routing; see the README pin table. ADC: GPIO40 battery, 41 5V rail, 42 board temperature.
GPIO44-47 are unused (ADC-capable spares).
RP2350-E9 check (every MCU pin): opto inputs GP2/3/6/7 4.7k down; SBC sense and service jumper 4.7k down; buttons, USB faults/PG, I2C, RUN pulled up;
GNSS PPS/RX 4.7k down (R94/R95); outputs have defined off-state resistors; ADC pins run with the digital input disabled; unused and expansion pins: see DESIGN_rev03.md.
Car radio peripheral board rev 0.4 - MG F (1996), VIM3 + RP2350B, 4ch line out on the audio module, NEO-M9N. Generated by gen4.py; see DESIGN_rev04.md.

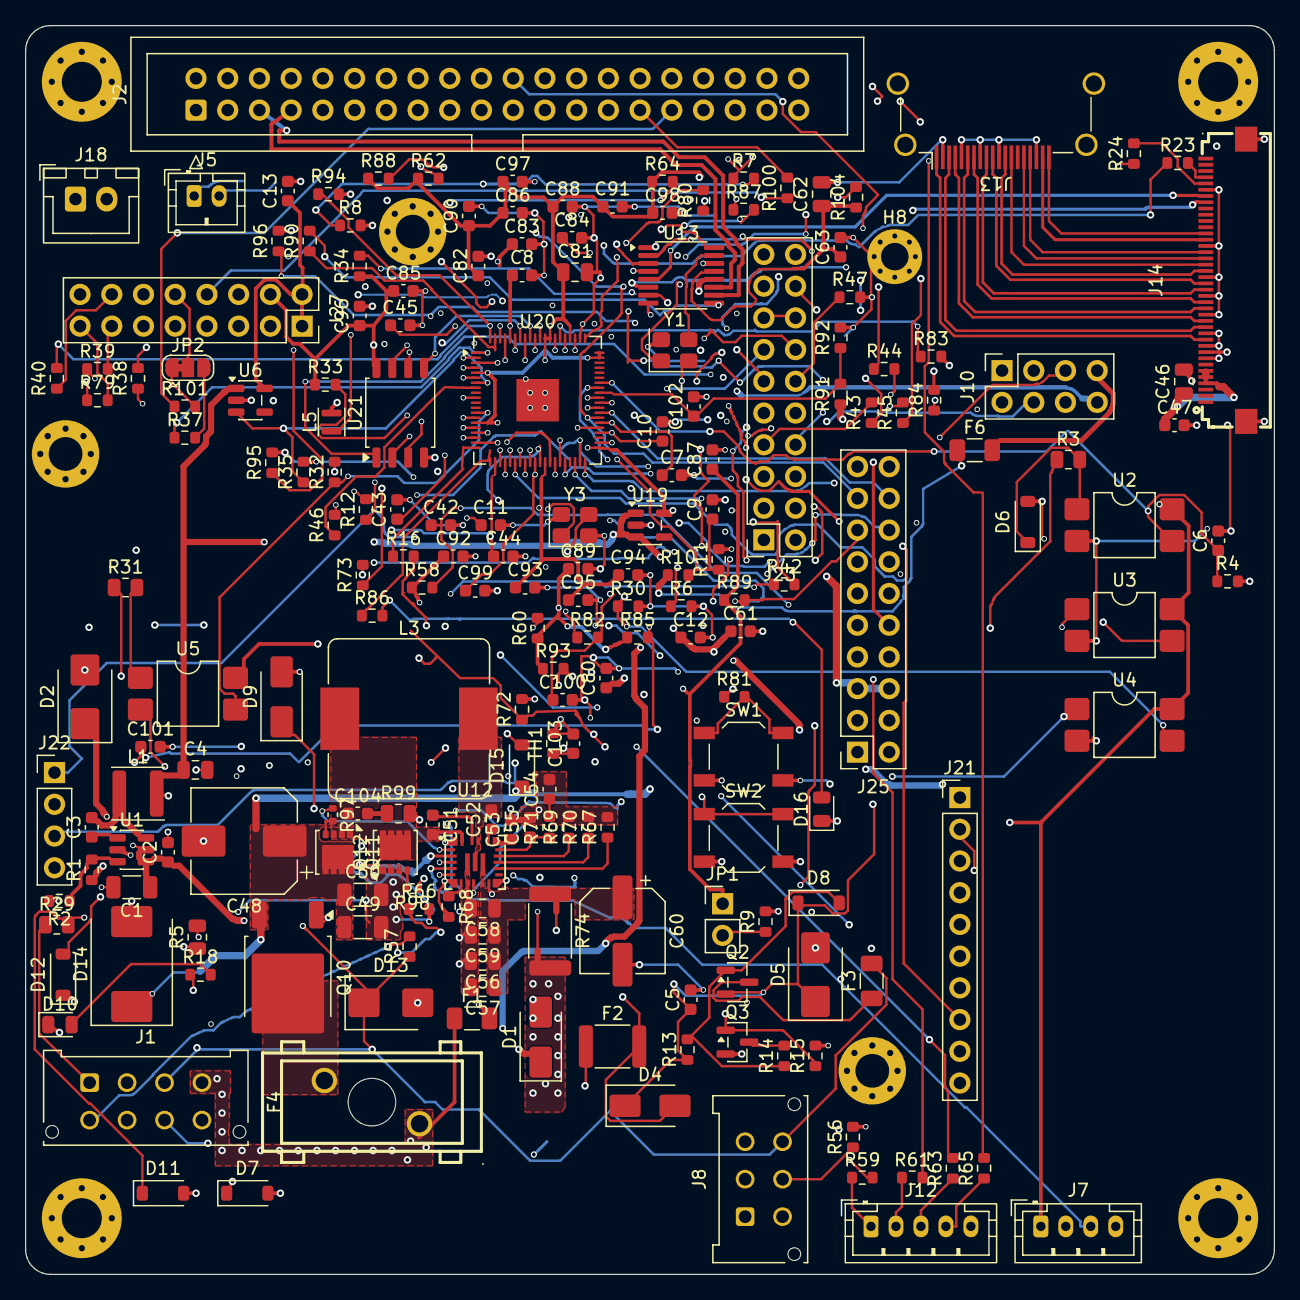
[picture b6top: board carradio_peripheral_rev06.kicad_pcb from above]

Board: 4 copper layers, 100.0 x 100.0 mm, 212 parts (1 on the bottom side), 175 nets.

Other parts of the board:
H1, H2, H3, H4: M3; MountingHole_3.2mm_M3_Pad_Via
H5: M2.5 standoff, USB module; MountingHole_2.7mm_M2.5_Pad_Via
H6: M2.5 standoff, audio module; MountingHole_2.7mm_M2.5_Pad_Via
H7: M2.5 standoff, GNSS module; MountingHole_2.7mm_M2.5_Pad_Via
H8: M2 standoff, K-line module; MountingHole_2.2mm_M2_Pad_Via

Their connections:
GND: H1.1, H2.1, H3.1, H4.1, H5.1, H6.1, H7.1, H8.1; also elsewhere on the board

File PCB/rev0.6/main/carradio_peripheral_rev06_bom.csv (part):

Designator,Value,Description / MPN,LCSC,Footprint (KiCad name),Fit,Note
J1,ISO 10487 A (via pigtail),Molex 43045-0812,C277661,Connector_Molex:Molex_Micro-Fit_3.0_43045-0812_2x04_P3.00mm_Vertical,yes,"pad n = ISO A pin n: A1 reverse lamp, A2 handbrake switch, A3 amp remote out, A4 +12V permanent, A5 remote (via R57), A6 illumination, A7 ACC, A8 GND"
F1,PTC 0.5A hold 30V,BHFUSE BSMD1206-050-30V,C883126,Fuse:Fuse_1206_3216Metric,yes,
F6,PTC 0.2A hold 30V,BHFUSE BSMD1206-020-30V,C883118,Fuse:Fuse_1206_3216Metric,yes,"own fuse for the K-line module battery feed, so a module fault cannot trip F1 (always-on supply)"
D1,SS34,SS34 40V 3A Schottky,C8678,Diode_SMD:D_SMA,yes,reverse-polarity protection
D2,SMBJ22A,SMBJ22A (BORN); alt DOWO C284010,C151920,Diode_SMD:D_SMB,yes,review 2026-09-29: 22V standoff survives a 24V jump start; 35.5V max clamp stays under the 38V limit of the TPS560430 and LMR33630
C1,10uF 50V,1206 10uF 50V X5R (Murata GRM31CR61H106KA12L),C77092,Capacitor_SMD:C_1206_3216Metric,yes,
C2,100nF,0603 100nF 50V X7R,C14663,Capacitor_SMD:C_0603_1608Metric,yes,
U1,TPS560430XDBVR,"TPS560430XDBVR 36V 600mA buck, 1.1MHz",C524782,Package_TO_SOT_SMD:SOT-23-6,yes,pinout checked against TI datasheet
C3,100nF,0603 100nF 50V X7R,C14663,Capacitor_SMD:C_0603_1608Metric,yes,
L1,18uH,"cjiang FNR4030S180MT 18uH 4x4mm shielded, Isat 1.5A, Irms 1.2A, 260 mOhm (SWPA4030S180MT C96895 discontinued at LCSC)",C167882,Inductor_SMD:L_Sunlord_SWPA4030S,yes,
R1,100k,0603 100k 1%,C25803,Resistor_SMD:R_0603_1608Metric,yes,
R2,24k,0603 24k 1%,C23352,Resistor_SMD:R_0603_1608Metric,yes,Vout = 1.0V x (1 + 100k/24k) = 5.17V
C4,22uF,0805 22uF 25V X5R,C45783,Capacitor_SMD:C_0805_2012Metric,yes,
F2,PTC 0.75A hold 30V,Littelfuse 1812L075/33DR,C151170,Fuse:Fuse_1812_4532Metric,yes,
D4,SS34,SS34 40V 3A Schottky,C8678,Diode_SMD:D_SMA,yes,
D5,SMBJ22A,SMBJ22A (BORN); alt DOWO C284010,C151920,Diode_SMD:D_SMB,yes,review 2026-09-29: 22V standoff survives a 24V jump start; 35.5V max clamp stays under the 38V limit of the TPS560430 and LMR33630
C5,100nF,0603 100nF 50V X7R,C14663,Capacitor_SMD:C_0603_1608Metric,yes,
R3,4.7kΩ 0805,0805 4.7k 1%,C17673,Resistor_SMD:R_0805_2012Metric,yes,
D6,1N4148W,1N4148W,C81598,Diode_SMD:D_SOD-123,yes,reverse-voltage clamp across opto LED
U2,EL817S1(C),EL817S1(C)(TU)-F (EL817S1(C)(TU)-FV),C470884,Package_DIP:SMDIP-4_W7.62mm,yes,
R4,4.7k,0603 4.7k 1%,C23162,Resistor_SMD:R_0603_1608Metric,yes,
C6,100nF,0603 100nF 50V X7R,C14663,Capacitor_SMD:C_0603_1608Metric,yes,
R5,4.7kΩ 0805,0805 4.7k 1%,C17673,Resistor_SMD:R_0805_2012Metric,yes,
D7,1N4148W,1N4148W,C81598,Diode_SMD:D_SOD-123,yes,reverse-voltage clamp across opto LED
U3,EL817S1(C),EL817S1(C)(TU)-F (EL817S1(C)(TU)-FV),C470884,Package_DIP:SMDIP-4_W7.62mm,yes,
R6,4.7k,0603 4.7k 1%,C23162,Resistor_SMD:R_0603_1608Metric,yes,
C7,100nF,0603 100nF 50V X7R,C14663,Capacitor_SMD:C_0603_1608Metric,yes,
R29,4.7kΩ 0805,0805 4.7k 1%,C17673,Resistor_SMD:R_0805_2012Metric,yes,
D11,1N4148W,1N4148W,C81598,Diode_SMD:D_SOD-123,yes,reverse-voltage clamp across opto LED
U4,EL817S1(C),EL817S1(C)(TU)-F (EL817S1(C)(TU)-FV),C470884,Package_DIP:SMDIP-4_W7.62mm,yes,
R30,4.7k,0603 4.7k 1%,C23162,Resistor_SMD:R_0603_1608Metric,yes,
C10,100nF,0603 100nF 50V X7R,C14663,Capacitor_SMD:C_0603_1608Metric,yes,
R31,4.7kΩ 0805,0805 4.7k 1%,C17673,Resistor_SMD:R_0805_2012Metric,yes,"PARK input: LED fed from ACC, handbrake switch pulls cathode to ground"
U5,EL817S1(C),EL817S1(C)(TU)-F (EL817S1(C)(TU)-FV),C470884,Package_DIP:SMDIP-4_W7.62mm,yes,
D12,1N4148W,1N4148W,C81598,Diode_SMD:D_SOD-123,yes,series diode: blocks reverse voltage when ACC is off
R32,4.7k,0603 4.7k 1%,C23162,Resistor_SMD:R_0603_1608Metric,yes,
C11,100nF,0603 100nF 50V X7R,C14663,Capacitor_SMD:C_0603_1608Metric,yes,
C8,100nF,0603 100nF 50V X7R,C14663,Capacitor_SMD:C_0603_1608Metric,yes,
R57,0Ω,0603 0 1%,C21189,Resistor_SMD:R_0603_1608Metric,DNP,DNP: fit to also put the amp remote on ISO A5 (the usual antenna/amp remote pin)
Q2,P-MOSFET -60V,onsemi FDN5618P -60V P-MOSFET (check 1=G 2=S 3=D in datasheet),C400792,Package_TO_SOT_SMD:SOT-23,yes,review: AO3401A (-30V) was below the 35.5V TVS clamp
R13,10k,YAGEO RC0603FR-0710KL 0603 10k 1%,C98220,Resistor_SMD:R_0603_1608Metric,yes,
D8,BZT52C12,BZT52C12-7-F 12V zener,C124196,Diode_SMD:D_SOD-123,yes,Vgs clamp
R14,10k,YAGEO RC0603FR-0710KL 0603 10k 1%,C98220,Resistor_SMD:R_0603_1608Metric,yes,
Q3,2N7002,JSCJ 2N7002,C8545,Package_TO_SOT_SMD:SOT-23,yes,"review: drain sees ACC through R13, so it needs more than 30V"
R16,100Ω,0603 100 1%,C22775,Resistor_SMD:R_0603_1608Metric,yes,
R15,100k,0603 100k 1%,C25803,Resistor_SMD:R_0603_1608Metric,yes,amp off while the MCU is in reset
F3,PTC 0.5A hold 30V,BHFUSE BSMD1206-050-30V,C883126,Fuse:Fuse_1206_3216Metric,yes,own fuse: a shorted remote wire cannot pull down ACC
D9,SS34,SS34 40V 3A Schottky,C8678,Diode_SMD:D_SMA,yes,clamps inductive kick from the remote wire
D13,SMBJ22A,SMBJ22A (BORN); alt DOWO C284010,C151920,Diode_SMD:D_SMB,yes,review 2026-09-29: 22V standoff survives a 24V jump start; 35.5V max clamp stays under the 38V limit of the TPS560430 and LMR33630
R18,4.7k,0603 4.7k 1%,C23162,Resistor_SMD:R_0603_1608Metric,yes,
D10,LED green,KT-0805G green LED,C2297,LED_SMD:LED_0805_2012Metric,yes,amp remote on
R7,1k,0603 1k 1%,C21190,Resistor_SMD:R_0603_1608Metric,yes,VIM3 on/off sense
R8,4.7k,0603 4.7k 1%,C23162,Resistor_SMD:R_0603_1608Metric,yes,
R10,1M,0603 1M 1%,C22935,Resistor_SMD:R_0603_1608Metric,yes,battery sense: 14.4V -> 2.6V
R11,220k,0603 220k 1%,C22961,Resistor_SMD:R_0603_1608Metric,yes,
C9,100nF,0603 100nF 50V X7R,C14663,Capacitor_SMD:C_0603_1608Metric,yes,
JP1,SERVICE jumper,1x2 male header 2.54mm + jumper cap C5305,C124375,Connector_PinHeader_2.54mm:PinHeader_1x02_P2.54mm_Vertical,yes,
R9,4.7k,0603 4.7k 1%,C23162,Resistor_SMD:R_0603_1608Metric,yes,
J10,K-line module socket,"CJT A2541HWV-2x4P 2x4 2.54mm female socket, 8.5mm body",C239344,Connector_PinSocket_2.54mm:PinSocket_2x04_P2.54mm_Vertical,yes,"K-line module plugs in here: 3V3, UART TX/RX (GP32/GP33), enable (GP28), VBAT_KLINE (via F6), 5V_AON"
U6,LP5907MFX-3.3,TI LP5907MFX-3.3/NOPB 250mA LDO (TECH PUBLIC TPLP5907MFX-3.3 clone; TI part out of stock at LCSC),C5370990,Package_TO_SOT_SMD:SOT-23-5,yes,"GNSS supply, switched by MCU GP9"
C12,1uF,0603 1uF 50V X5R (Murata GRM188R61H105KAALD),C77386,Capacitor_SMD:C_0603_1608Metric,yes,
R35,100k,0603 100k 1%,C25803,Resistor_SMD:R_0603_1608Metric,yes,GNSS off by default
C13,1uF,0603 1uF 50V X5R (Murata GRM188R61H105KAALD),C77386,Capacitor_SMD:C_0603_1608Metric,yes,
R37,1k,0603 1k 1%,C21190,Resistor_SMD:R_0603_1608Metric,yes,
R38,1k,0603 1k 1%,C21190,Resistor_SMD:R_0603_1608Metric,yes,
R39,1k,0603 1k 1%,C21190,Resistor_SMD:R_0603_1608Metric,yes,firmware drives low only to reset
R40,1k,0603 1k 1%,C21190,Resistor_SMD:R_0603_1608Metric,yes,
R100,1k,0603 1k 1%,C21190,Resistor_SMD:R_0603_1608Metric,yes,GNSS NMEA also to VIM3 UART_C (header pin 15) for the existing GNSS HAL / kernel gnss driver
R101,1k,0603 1k 1%,C21190,Resistor_SMD:R_0603_1608Metric,yes,VIM3 UART_C TX (header pin 16)
JP2,GNSS RX source,"3-pad solder jumper (PCB copper, no part)",,Jumper:SolderJumper-3_P1.3mm_Bridged12_RoundedPad1.0x1.5mm,yes,"who talks to the receiver: 1-2 (default, bridged) = VIM3 UART_C, 2-3 = MCU UART0. GNSS TX always goes to both."
J27,GNSS module socket,"kinghelm KH-2.54FH-2X8P-H8.5 2x8 2.54mm female socket, 8.5mm body",C22440830,Connector_PinSocket_2.54mm:PinSocket_2x08_P2.54mm_Vertical,yes,"GNSS module plugs in here: switched 3V3 (U6), backup 3V3, UART, USB, reset, PPS, safeboot"
U22,AQY210S,"Panasonic AQY210S PhotoMOS 350V 120mA 1 Form A, SOP-4 (own stock)",,Package_SO:SO-4_4.4x4.3mm_P2.54mm,yes,"bottom side next to J5. Output shorts the two J5 pins (the VIM3 POWER key pads), isolated; LED from GPIO15 through R12"
R12,390Ω,UNI-ROYAL 0603WAF3900T5E 390 1%,C23151,Resistor_SMD:R_0603_1608Metric,yes,"U22 LED current, ~5 mA from 3.3 V"
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
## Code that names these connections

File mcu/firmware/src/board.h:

// RP2350B pin map for the car radio peripheral board, rev 0.6.
//
// Taken from the rev 0.6 main-board netlist (PCB/rev0.6/main/carradio_peripheral_rev06.net,
// U20). The comment after each pin names the net and the parts that set its idle level.
#pragma once

#define BOARD_REV 6

// ---- Car inputs: EL817 opto, emitter to the pin, 4.7k pull-down. High = 12V present. ----
#define PIN_ACC_IN        43  // /MCU_ACC_IN    U2, R4 (ISO A7, via F2)
#define PIN_ILLUM_IN      37  // /MCU_ILLUM_IN  U3, R6 (ISO A6)
#define PIN_REV_IN        35  // /MCU_REV_IN    U4, R30 (ISO A1)
#define PIN_PARK_IN       14  // /MCU_PARK_IN   U5, R32 (ISO A2, switch to ground; open = released)

// ---- Other inputs ----
#define PIN_SBC_SENSE      6  // /MCU_SBC_SENSE  VIM3 3.3V via R7 1k, R8 4.7k pull-down. High = VIM3 on
#define PIN_SERVICE       19  // /MCU_SERVICE    JP1 to 3.3V, R9 4.7k pull-down. High = service mode
#define PIN_USBP_PG       36  // /MCU_USBP_PG    USB module LMR33630 PG, R89 10k pull-up. High = good
#define PIN_USBP_FAULT1   39  // /MCU_USBP_FAULT1 TPS2561 FAULT, R87 10k pull-up. Low = over-current
#define PIN_USBP_FAULT2   38  // /MCU_USBP_FAULT2 R88 10k pull-up. Low = over-current
#define PIN_GNSS_PPS       3  // /MCU_GNSS_PPS   via R40 1k, R94 4.7k pull-down

// ---- Display buttons J12: switch to GND, 10k pull-up, 1k + 100nF RC. Low = pressed ----
#define PIN_BTN_SCREEN    18  // /MCU_BTN_SCREEN J12.1
#define PIN_BTN_VOLUP     17  // /MCU_BTN_VOLUP  J12.2
#define PIN_BTN_VOLDN     22  // /MCU_BTN_VOLDN  J12.3
#define PIN_BTN_MUTE      16  // /MCU_BTN_MUTE   J12.4

// ---- Outputs ----
#define PIN_VIM3_PWR_EN   23  // /MCU_VIM3_PWR_EN R73 1k -> TPS55288 EN + USB module enable; R72 100k pull-down
#define PIN_PWR_KEY       15  // /MCU_PWR_KEY    R12 390R -> AQY210S U22 LED. High = VIM3 power key pressed
#define PIN_AMP_EN        20  // /MCU_AMP_EN     R16 -> Q3 2N7002 -> amp remote (ISO A3). R15 pull-down
#define PIN_BL_EN          0  // /MCU_BL_EN      R23 -> panel FPC pin 37. R96 100k pull-down
#define PIN_BL_PWM         1  // /MCU_BL_PWM     R24 -> panel FPC pin 36. Inverted: low = brightest
#define PIN_DAC_MUTE      10  // /MCU_DAC_MUTE   R46 1k -> DAC XSMT, R47 10k pull-down. High = play
#define PIN_HUB_RST        2  // /MCU_HUB_RST    R90 1k -> CH334R RESET#, R104 10k pull-up. Drive low only
#define PIN_GNSS_EN        9  // /MCU_GNSS_EN    LP5907 U6 enable, R35 100k pull-down
#define PIN_GNSS_RST       7  // /MCU_GNSS_RST   R39 1k -> NEO RESET_N. Drive low only
#define PIN_GNSS_SAFEBOOT  8  // /MCU_GNSS_SAFEBOOT R79 1k -> NEO SAFEBOOT_N. Drive low only
#define PIN_LED           21  // /MCU_LED        R86 1k -> D16 green. High = on

// ---- UART1 to the GNSS (NEO-M9N UART1) ----
#define PIN_GNSS_TX        4  // /MCU_GNSS_TX    R37 -> GNSS RXD only when JP2 is set to 2-3
#define PIN_GNSS_RX        5  // /MCU_GNSS_RX    R38 from GNSS TXD, R95 4.7k pull-down
#define GNSS_UART          uart1

// ---- I2C1: BH1750 (J7), TPS55288 (U12), audio module, expansion J21. 4.7k pull-ups ----
#define PIN_I2C_SDA       30  // /LUX_SDA
#define PIN_I2C_SCL       31  // /LUX_SCL
#define BOARD_I2C          i2c1
#define TPS55288_ADDR     0x74  // MODE pin R67 = 0 ohm
#define BH1750_ADDR_L     0x23
#define BH1750_ADDR_H     0x5C

// ---- ADC (RP2350B: GPIO40..47 are ADC0..7) ----
#define PIN_VBAT_ADC      40  // ADC0 /MCU_VBAT_ADC  R10 1M / R11 220k from VBAT_P
#define PIN_5VSYS_ADC     41  // ADC1 /MCU_5VSYS_ADC R91 10k / R92 10k from +5V_SYS
#define PIN_TEMP_ADC      42  // ADC2 /MCU_TEMP_ADC  R93 10k to 3.3V, TH1 NTC 10k B3950 to GND
#define ADC_CH_VBAT        0
#define ADC_CH_5VSYS       1
#define ADC_CH_TEMP        2

// ---- K-line module socket J10 (PCB/kline_module_r01: L9637D on 3.3 V, no level shifting) ----
#define PIN_KLINE_TX      32  // /EXP_GP32 UART0 TX -> L9637D TX (low = K-line low)
#define PIN_KLINE_RX      33  // /EXP_GP33 UART0 RX <- L9637D RX (echoes our own TX too)
#define PIN_KLINE_EN      28  // /EXP_GP28 high = K-line side powered (Q2/Q1, green LED); R4 pull-down
#define KLINE_UART        uart0

// Pins with nothing on them or only on expansion headers (J21: GPIO24..27).
// RP2350-E9: these are parked as inputs with the input buffer off and no pulls.
#define UNUSED_PINS {11, 12, 13, 24, 25, 26, 27, 29, 34, 44, 45, 46, 47}

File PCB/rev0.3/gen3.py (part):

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cap("C11", "100n", 375, 109, "MCU_PARK_IN", "GND")
text("PARK (ISO A2, handbrake switch; may stay unwired)", 311, 83, 1.5)
cap("C8", "100n", 395, 60, "+3V3_MCU", "GND")
res("R57", "0", 545, 100, "AMP_REM", "ISO_A5", dnp=True, note="DNP: fit to also put the amp remote on ISO A5 (the usual antenna/amp remote pin)")
text("LED ~2.7mA at 14.4V; EL817 C-grade CTR >= 200%. 4.7k pull-downs satisfy RP2350-E9.", 215, 140)

# ================================================================ 3. amp remote
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res("R10", "1M", 146, 180, "VBAT_P", "MCU_VBAT_ADC", note="battery sense: 14.4V -> 2.6V")
res("R11", "220k", 154, 180, "MCU_VBAT_ADC", "GND")
cap("C9", "100n", 162, 180, "MCU_VBAT_ADC", "GND")
place(CG2, "JP1", "SERVICE jumper", 135, 215, {"1": "+3V3_MCU", "2": "MCU_SERVICE"}, "Connector_PinHeader_2.54mm:PinHeader_1x02_P2.54mm_Vertical", "", "1x2 2.54mm pin header + jumper")
res("R9", "4.7k", 150, 218, "MCU_SERVICE", "GND")
place(CG8, "J10", "Expansion", 185, 205, {"1": "+3V3_MCU", "2": "EXP_GP20", "3": "EXP_GP21", "4": "EXP_GP30", "5": "+5V_AON", "6": "GND", "7": "GND", "8": "EXP_GP31"},
      "Connector_PinHeader_2.54mm:PinHeader_1x08_P2.54mm_Vertical", "", "1x8 2.54mm pin header",
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       "3": "SDR_DM", "4": "SDR_DP", "1": "HUB2_UP_DM", "2": "HUB2_UP_DP"},
      "Package_SO:QSOP-16_3.9x4.9mm_P0.635mm", "C4154405", "WCH CH334R 4-port USB 2.0 hub, QSOP-16",
      note="pinout checked against WCH CH334 datasheet (CH334R column). Upstream = VIM3 header pins 3/4 (VIM3 hub port 4)")
place(add_lib('Device', 'Crystal_GND24'), "Y1", "12MHz", 660, 305, {"1": "HUB_XI", "3": "HUB_XO", "2": "GND", "4": "GND"}, "Crystal:Crystal_SMD_3225-4Pin_3.2x2.5mm", "",
      "12MHz crystal (pick in library)", note="CH334R has built-in load capacitors")
cap("C61", "1u", 720, 262, "+5V_SYS", "GND", note="at V5")
cap("C62", "10u", 728, 262, "HUB_3V3", "GND")
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       "10": "HUB2_UP_DM", "11": "HUB2_UP_DP", "7": "EXT1_DM", "8": "EXT1_DP", "5": "EXT2_DM", "6": "EXT2_DP", "3": None, "4": None, "1": None, "2": None},
      "Package_SO:QSOP-16_3.9x4.9mm_P0.635mm", "C4154405", "WCH CH334R 4-port USB 2.0 hub, QSOP-16",
      note="cascaded on hub 1 port 4. RESET#/CDP tied high = BC1.2 CDP for faster phone charging (WCH: depends on batch)")
place(add_lib('Device', 'Crystal_GND24'), "Y2", "12MHz", 530, 505, {"1": "HUB2_XI", "3": "HUB2_XO", "2": "GND", "4": "GND"}, "Crystal:Crystal_SMD_3225-4Pin_3.2x2.5mm", "", "12MHz crystal (pick in library)")
cap("C75", "1u", 580, 455, "+5V_SYS", "GND")
cap("C76", "10u", 588, 455, "HUB2_3V3", "GND")
cap("C77", "100n", 596, 455, "HUB2_3V3", "GND")
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               16: 16, 17: 17, 18: 18, 19: 19, 20: 20, 21: 21, 22: 22, 23: 23, 24: 25, 25: 26, 26: 27, 27: 28, 28: 36, 29: 37,
               30: 38, 31: 39, 32: 40, 33: 42, 34: 43, 35: 44, 36: 45, 37: 46, 38: 47, 39: 48,
               40: 49, 41: 52, 42: 53, 43: 54, 44: 55, 45: 56, 46: 57, 47: 58}
GPIO_NET = {0: "MCU_GNSS_TX", 1: "MCU_GNSS_RX", 2: "MCU_ACC_IN", 3: "MCU_REV_IN", 4: "LUX_SDA", 5: "LUX_SCL", 6: "MCU_ILLUM_IN",
            7: "MCU_PARK_IN", 8: "MCU_PWR_KEY", 9: "MCU_AMP_EN", 10: "MCU_BL_EN", 11: "MCU_BL_PWM", 12: "MCU_GNSS_EN",
            13: "MCU_SBC_SENSE", 14: "MCU_SERVICE", 15: "MCU_DAC_MUTE", 16: "MCU_BTN_SCREEN", 17: "MCU_BTN_VOLUP",
            18: "MCU_GNSS_RST", 19: "MCU_GNSS_PPS", 20: "EXP_GP20", 21: "EXP_GP21", 22: "MCU_BTN_VOLDN",
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for g, n in GPIO_NET.items(): rp_conns[str(RP_GPIO_PIN[g])] = n
for g in range(44, 48): rp_conns[str(RP_GPIO_PIN[g])] = None
place(RP, "U20", "RP2350B", 960, 150, rp_conns, "Package_DFN_QFN:QFN-80-1EP_10x10mm_P0.4mm_EP3.4x3.4mm", "", "Raspberry Pi RP2350B, QFN-80 (use the EasyEDA library footprint)",
      note="GPIO map in DESIGN_rev03.md. GPIO0-29 keep the rev 0.2 Pico numbers, except the battery ADC (GP26 -> GPIO40: only GPIO40-47 have ADC on the RP2350B)")

# 3.3V: low-quiescent LDO from the always-on 5.2V (the Pico module's own regulator is gone)
LDO33 = add_lib('Regulator_Linear', 'AP2112K-3.3')
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      note="place next to the TPS55288 / LMR33630: board temperature for thermal derating")
cap("C103", "100n", 916, 360, "MCU_TEMP_ADC", "GND")

# expansion: GPIO32-39
place(add_lib('Connector_Generic', 'Conn_01x10'), "J21", "Expansion 2", 1140, 200,
      {"1": "+3V3_MCU", "2": "EXP_GP32", "3": "EXP_GP33", "4": "EXP_GP34", "5": "EXP_GP35", "6": "EXP_GP36", "7": "EXP_GP37", "8": "EXP_GP38", "9": "EXP_GP39", "10": "GND"},
      "Connector_PinHeader_2.54mm:PinHeader_1x10_P2.54mm_Vertical", "", "1x10 2.54mm pin header", note="spare GPIO32-39 (e.g. CAN, extra UART/SPI)")
text("GPIO0-29 as rev 0.2 except: GPIO40 battery ADC (was GP26), GPIO23/24 USB port faults, GPIO25 LED, GPIO26 USB supply PG,", 860, 400)
text("GPIO29 GNSS safeboot, GPIO30/31 on J10, GPIO32-39 on J21, GPIO41 5V rail ADC, GPIO42 board temperature, GPIO43 hub 1 reset.", 860, 404)

# RP2350-E9 (input pad can latch near 2V with only the internal pull-down): every MCU input that can float
# gets an external resistor. Pull-downs are 4.7k (below the ~8.2k the erratum workaround calls for).
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
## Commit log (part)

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2025-11-20 Add a hal
2025-11-20 New Implementation
2025-11-20 Update vehicle_ndk to v3
2025-11-20 Fix import
2025-11-20 Implement missing methods
2025-11-20 First compiling HAL
2025-11-20 configure emulator
2025-11-20 Use system properties for device paths
2025-11-20 Refactor code for readability
2025-11-23 Update SDK Version
2025-11-25 add evs config
2025-11-25 Fix file conflict
2025-12-06 Update HAL
2025-12-06 rename evs
2025-12-06 Remove libgpiod
2025-12-06 No exceptions
2025-12-07 Fix paths
2025-12-08 Resolve pwm controller based on memory adress
2025-12-08 PWM fix:now working on boot, screen might still flicker on adjustment. Timing improvements required
2025-12-09 Add debouncing to kernel writes
    Make sure that we are not spamming the kernel when changing brightness,
    If the level is the same, dont write it to the sysfs endpoint
2025-12-09 Add bh1750 support
2025-12-09 Fix pwm init
2025-12-10 Optimize init sequence for slow kernel
2025-12-10 Fix pwm enable
2025-12-22 Add audio controll hal
2025-12-23 Fix build
2026-01-04 Add controll
2026-01-04 Add Balance and fader apps
2026-01-09 FeatureDump
2026-01-10 Update VHAL for gear polling
2026-01-12 Fix Pin Allocation
2026-01-13 Do not close file handle for gpio pin
2026-01-14 Fix reverse camera detection
2026-01-14 Add fallback if variable is undefined
2026-01-21 Test c++ rvc service
2026-01-26 Force VHAL to report parked
2026-01-30 Add gnss usb serial service
2026-02-15 enable scanning of AML serial devices
2026-02-19 Fixes for GPS and Lineage 23.2
2026-03-08 Add RRO for power button override
2026-05-03 Fix VHAL for gear selection
2026-05-06 Reboot wifi to fix co-existence
2026-05-10 Add AA RRO
2026-06-28 Add pi pico firmware for vim3 input controll
